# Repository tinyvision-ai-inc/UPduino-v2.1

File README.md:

# UPduino v2.1

## UPDuino v2.1: PCB Design Files, Designs, Documentation

The UPDuino v2.1 is a small, low cost FPGA board, built with license from Lattice Semiconductor. The board features an on-board FPGA programmer, flash and LED with all pins brought out to easy to use 0.1" header pins for fast prototyping.

The tinyVision.ai UPduino v2.1 Board Features:

* Lattice UltraPlus ICE40UP5K FPGA with 5.3K LUTs, 1Mb SPRAM, 120Kb DPRAM, 8 Multipliers
* FTDI FT232H USB to SPI Device
* 30 GPIO on 0.1” headers
* 4MB SPI Flash
* RGB LED
* On board 3.3V and 1.2V Regulators, can supply 3.3V to your project
* Open source schematic and layout using Eagle PCB design tools
* Integrated into the open source [APIO toolchain](https://github.com/FPGAwars/apio)
* Improved USB footprint to minimize connectors ripping off the board

### Please fill out the [next generation survey](https://www.surveymonkey.com/r/HH536D8) to suggest improvements to this board. We really appreciate the feedback and will make improvements as business permits!

You can buy the board here:

## Useful links
* [osresearch](https://github.com/osresearch/up5k): large collection of very useful code and a good overview.
* [UPduino FPGA tutorial using APIO](https://blog.idorobots.org/entries/upduino-fpga-tutorial.html)
* [A very detailed blog on implementing a RISCV in the FPGA](https://pingu98.wordpress.com/2019/04/08/how-to-build-your-own-cpu-from-scratch-inside-an-fpga/)
* [FuPY](https://fupy.github.io/) MicroPython on FPGA's!
* [Migen](https://github.com/m-labs/migen) Python as a High Level tool to generate HW

## Differences between the v2.0 and v2.1 hardware
The original design for the UPduino v2.0 was from [GnarlyGrey](http://gnarlygrey.com/). The design for the UPduino was transferred to tinyVision.ai by Lattice Semiconductor recently. The board is already in use for a variety of projects but some improvements were necessary to make this more production friendly. Note that this exercise was a minimal change only!
* Changed soldermask to black to make it easy to identify the v2.0 from v2.1 and also for branding purposes. Added tinyVision logo to silkscreen.
* Replaced micro USB surface mount connector with through hole parts. This reduces the probability of the USB connector ripping off from the PWB.
* Unified resistor and capacitor sizes to 0603 from a mix of 0603/0805 footprints
* Added fiducials to the board for manufacturability
* LED and resonator went end of life. Replaced the LED with [this](https://www.mouser.com/ProductDetail/Broadcom-Avago/ASMB-MTB0-0A3A2?qs=%2Fha2pyFaduiVySQcEVUF3g99inKvemcQFBZprfU%2FW0p9YdxM%252BOGCOQ%3D%3D) one and the resonator with [this](https://www.mouser.com/ProductDetail/Murata-Electronics/CSTNE12M0G550000R0?qs=sGAEpiMZZMsBj6bBr9Q9aVicrFFkOfIYlp58nnUM76JPeseMdQedBQ%3D%3D) one.
* Flash used is the [Winbond W25Q32JVSNIM](https://www.mouser.com/ProductDetail/Winbond/W25Q32JVSNIM?qs=sGAEpiMZZMtI%252BQ06EiAoG4%252BhDIVn9lGKlH%2FgDg3lStQ%3D)
* Boards are built in Carlsbad, CA from parts sourced from Digikey/Mouser so known good, non-recycled parts are used. We use a cool [vapor phase reflow](https://www.westfloridacomponents.com/blog/vapor-phase-reflow-soldering/)!
* Testing: Each board is inspected using [AOI](https://en.wikipedia.org/wiki/Automated_optical_inspection) to ensure all parts are placed properly. Each board is programmed with a blinking LED to ensure the parts come up and the LED is alive. Also the FTDI EEPROM is programmed with some details.

## Announcing v3.0!
Thank you for the continued feedback which has been incorporated into the [new 3.0 design ](https://github.com/tinyvision-ai-inc/UPduino-v3.0)

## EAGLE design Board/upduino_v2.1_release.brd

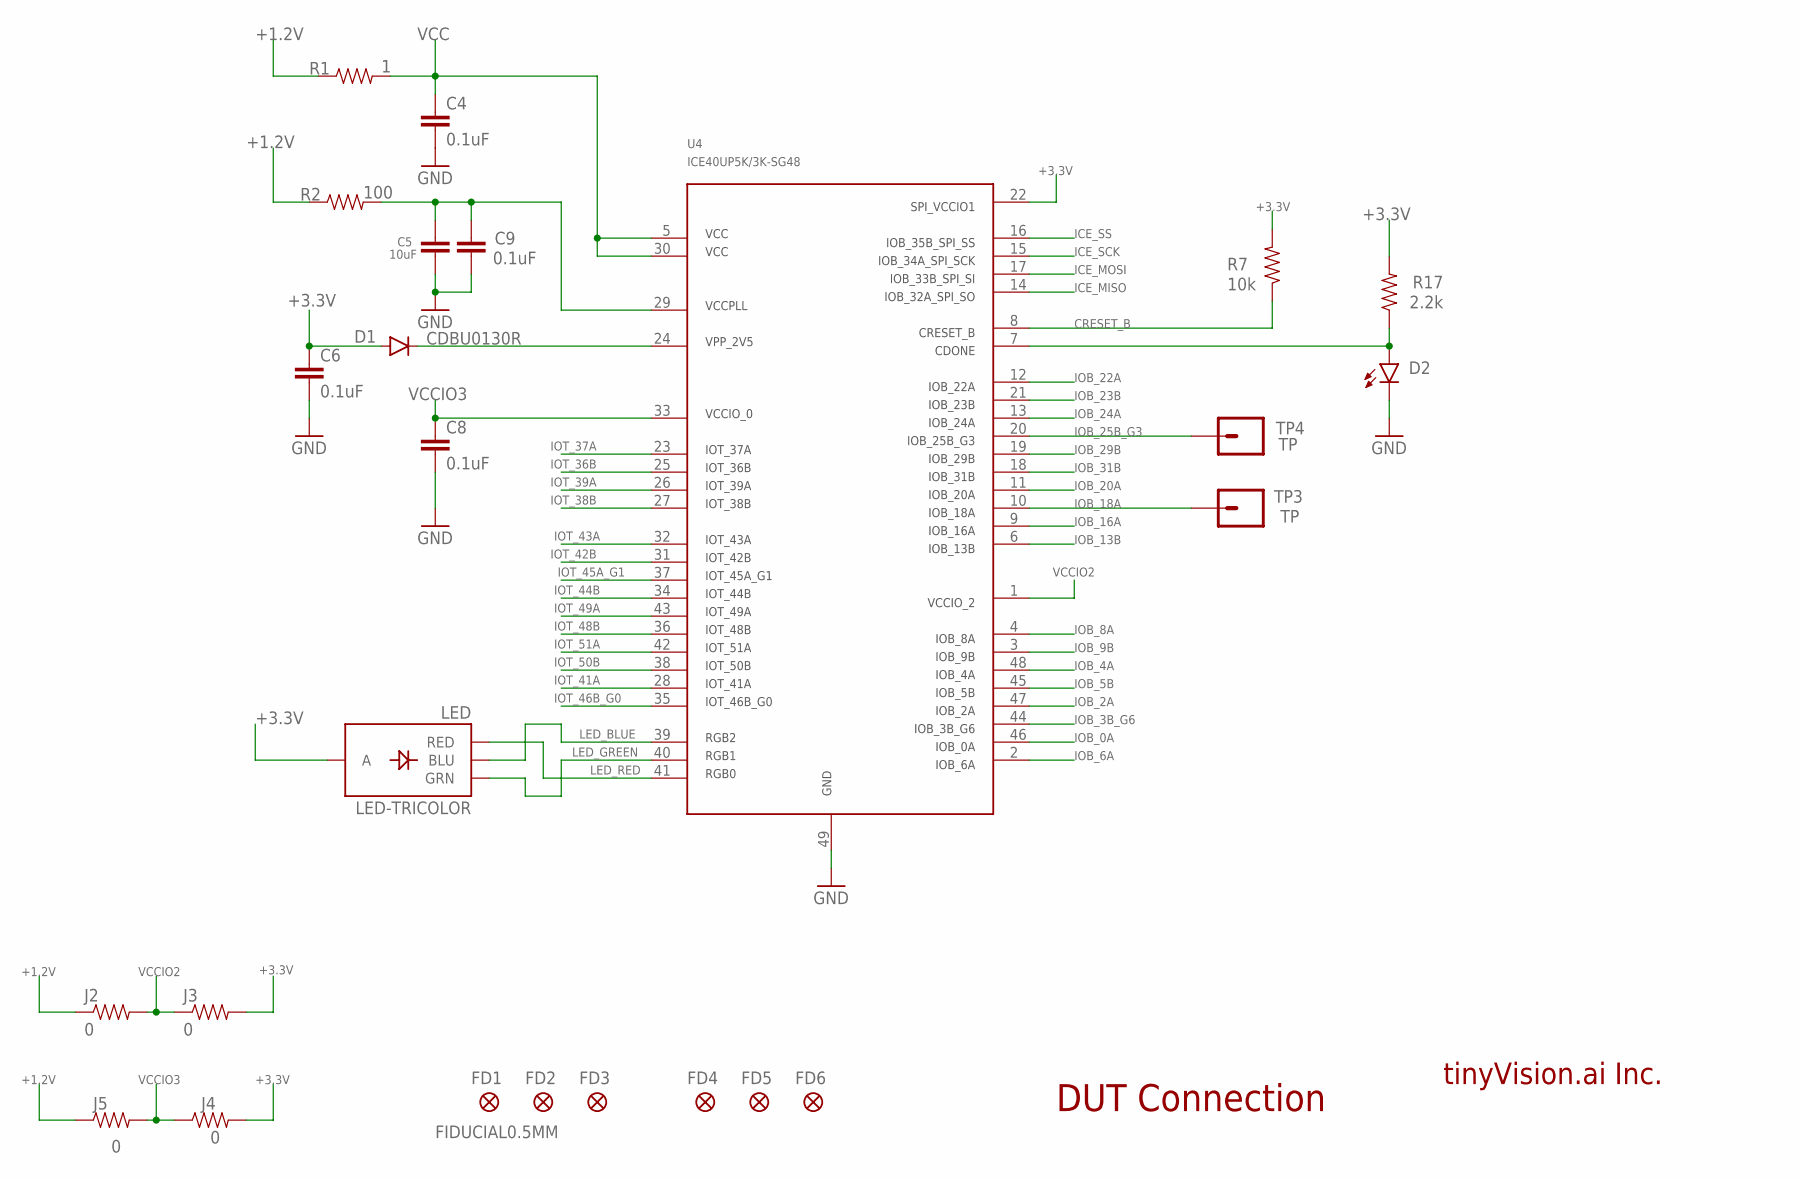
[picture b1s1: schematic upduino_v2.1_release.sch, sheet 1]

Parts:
C4, C6, C8, C9: 0.1uF; 0603-CAP
C5: 10uF; 0603-CAP
D1: CDBU0130R; SOD523
D2: LED0603; LED-0603
FD1, FD2, FD3, FD4, FD5, FD6: FIDUCIAL0.5MM; FIDUCIAL_0.5MM
J2, J3, J4, J5: 0; 0603-RES
LED: LED-TRICOLOR; LED-TRICOLOR-SMD
R1: 1; 0603-RES
R2: 100; 0603-RES
R7: 10k; 0603-RES
R17: 2.2k; 0603-RES
TP3, TP4: TP
U4: ICE40UP5K/3K-SG48

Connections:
+1.2V: J2.1, J5.1, R1.1, R2.1; also elsewhere on the board
+3.3V: C6.1, D1.A, J3.2, J4.2, LED.A, R7.2, R17.2, U4.22; also elsewhere on the board
CRESET_B: R7.1, U4.8; also elsewhere on the board
GND: C4.2, C5.2, C6.2, C8.2, C9.2, D2.C, U4.49; also elsewhere on the board
ICE_MISO: U4.14; also elsewhere on the board
ICE_MOSI: U4.17; also elsewhere on the board
ICE_SCK: U4.15; also elsewhere on the board
ICE_SS: U4.16; also elsewhere on the board
IOB_0A: U4.46; also elsewhere on the board
IOB_2A: U4.47; also elsewhere on the board
IOB_3B_G6: U4.44; also elsewhere on the board
IOB_4A: U4.48; also elsewhere on the board
IOB_5B: U4.45; also elsewhere on the board
IOB_6A: U4.2; also elsewhere on the board
IOB_8A: U4.4; also elsewhere on the board
IOB_9B: U4.3; also elsewhere on the board
IOB_13B: U4.6; also elsewhere on the board
IOB_16A: U4.9; also elsewhere on the board
IOB_18A: TP3.1, U4.10
IOB_20A: U4.11; also elsewhere on the board
IOB_22A: U4.12; also elsewhere on the board
IOB_23B: U4.21; also elsewhere on the board
IOB_24A: U4.13; also elsewhere on the board
IOB_25B_G3: TP4.1, U4.20
IOB_29B: U4.19; also elsewhere on the board
IOB_31B: U4.18; also elsewhere on the board
IOT_36B: U4.25; also elsewhere on the board
IOT_37A: U4.23; also elsewhere on the board
IOT_38B: U4.27; also elsewhere on the board
IOT_39A: U4.26; also elsewhere on the board
IOT_41A: U4.28; also elsewhere on the board
IOT_42B: U4.31; also elsewhere on the board
IOT_43A: U4.32; also elsewhere on the board
IOT_44B: U4.34; also elsewhere on the board
IOT_45A_G1: U4.37; also elsewhere on the board
IOT_46B_G0: U4.35; also elsewhere on the board
IOT_48B: U4.36; also elsewhere on the board
IOT_49A: U4.43; also elsewhere on the board
IOT_50B: U4.38; also elsewhere on the board
IOT_51A: U4.42; also elsewhere on the board
LED_BLUE: LED.B (BLU), U4.39
LED_GREEN: LED.G (GRN), U4.40
LED_RED: LED.R (RED), U4.41
unnamed: C5.1, C9.1, R2.2, U4.29
unnamed: D1.C, U4.24
unnamed: D2.A, R17.1, U4.7
VCC: C4.1, R1.2, U4.5, U4.30
VCCIO2: J2.2, J3.1, U4.1
VCCIO3: C8.1, J4.1, J5.2, U4.33

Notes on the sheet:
DUT Connection
tinyVision.ai Inc.

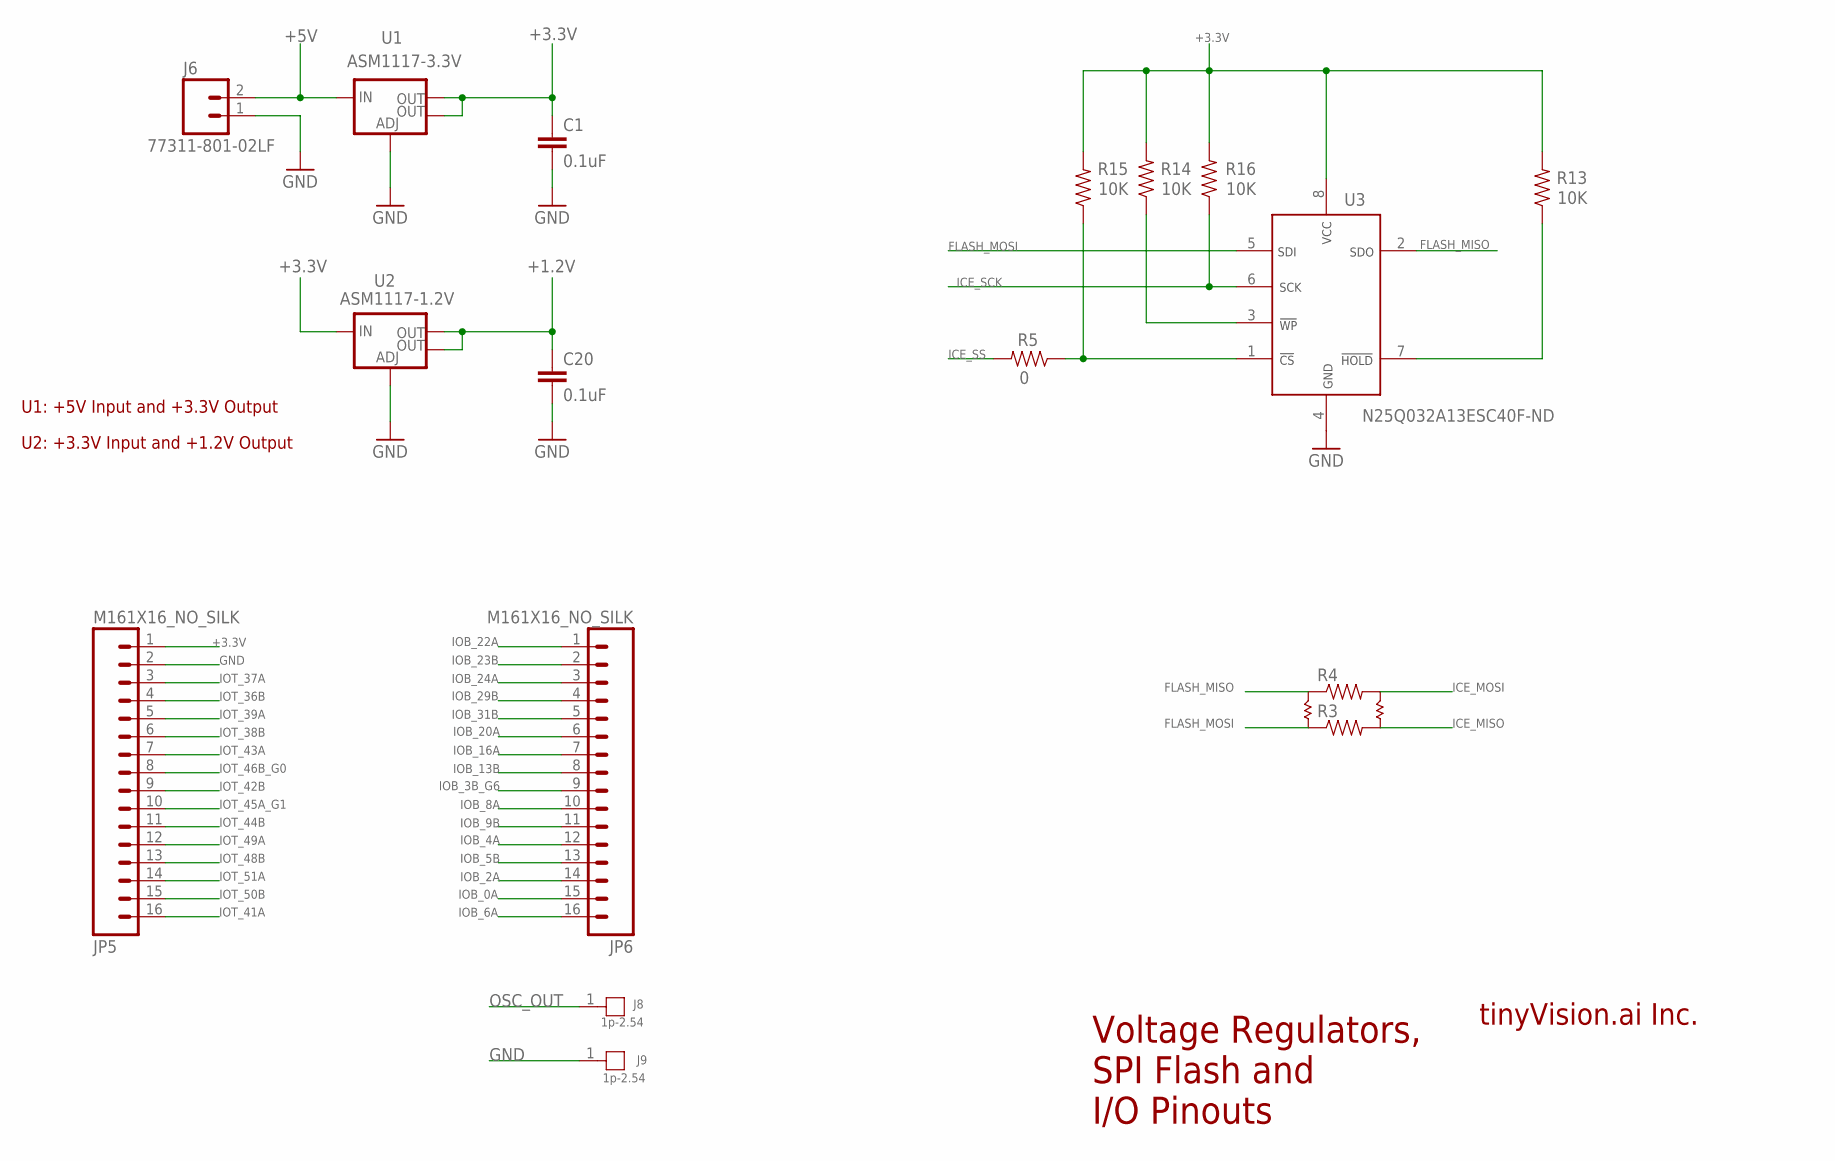
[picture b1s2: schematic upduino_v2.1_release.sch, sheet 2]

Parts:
C1, C20: 0.1uF; 0603-CAP
J6: 77311-801-02LF; 1X02
J8, J9: 1p-2.54; 1P-65/35MIL
JP5, JP6: M161X16_NO_SILK; 1X16_NO_SILK
R3, R4: RESISTOR0603; 0603-RES
R5: 0; 0603-RES
R13, R14, R15, R16: 10K; 0603-RES
U1: ASM1117-3.3V; SOT223
U2: ASM1117-1.2V; SOT223
U3: N25Q032A13ESC40F-ND; SO8; MPN N25Q032A13ESC40F-ND

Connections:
+1.2V: C20.1, U2.2 (OUT), U2.4 (OUT); also elsewhere on the board
+3.3V: C1.1, JP5.1, R13.2, R14.2, R15.2, R16.2, U1.2 (OUT), U1.4 (OUT), U2.3 (IN), U3.8; also elsewhere on the board
+5V: J6.2, U1.3 (IN); also elsewhere on the board
FLASH_MISO: R4.1, U3.2; also elsewhere on the board
FLASH_MOSI: R3.1, U3.5; also elsewhere on the board
GND: C1.2, C20.2, J6.1, J9.1, JP5.2, U1.1 (ADJ), U2.1 (ADJ), U3.4; also elsewhere on the board
ICE_MISO: R3.2; also elsewhere on the board
ICE_MOSI: R4.2; also elsewhere on the board
ICE_SCK: R16.1, U3.6; also elsewhere on the board
ICE_SS: R5.2; also elsewhere on the board
IOB_0A: JP6.15; also elsewhere on the board
IOB_2A: JP6.14; also elsewhere on the board
IOB_3B_G6: JP6.9; also elsewhere on the board
IOB_4A: JP6.12; also elsewhere on the board
IOB_5B: JP6.13; also elsewhere on the board
IOB_6A: JP6.16; also elsewhere on the board
IOB_8A: JP6.10; also elsewhere on the board
IOB_9B: JP6.11; also elsewhere on the board
IOB_13B: JP6.8; also elsewhere on the board
IOB_16A: JP6.7; also elsewhere on the board
IOB_20A: JP6.6; also elsewhere on the board
IOB_22A: JP6.1; also elsewhere on the board
IOB_23B: JP6.2; also elsewhere on the board
IOB_24A: JP6.3; also elsewhere on the board
IOB_29B: JP6.4; also elsewhere on the board
IOB_31B: JP6.5; also elsewhere on the board
IOT_36B: JP5.4; also elsewhere on the board
IOT_37A: JP5.3; also elsewhere on the board
IOT_38B: JP5.6; also elsewhere on the board
IOT_39A: JP5.5; also elsewhere on the board
IOT_41A: JP5.16; also elsewhere on the board
IOT_42B: JP5.9; also elsewhere on the board
IOT_43A: JP5.7; also elsewhere on the board
IOT_44B: JP5.11; also elsewhere on the board
IOT_45A_G1: JP5.10; also elsewhere on the board
IOT_46B_G0: JP5.8; also elsewhere on the board
IOT_48B: JP5.13; also elsewhere on the board
IOT_49A: JP5.12; also elsewhere on the board
IOT_50B: JP5.15; also elsewhere on the board
IOT_51A: JP5.14; also elsewhere on the board
unnamed: R13.1, U3.7
unnamed: R14.1, U3.3
unnamed: R5.1, R15.1, U3.1
OSC_OUT: J8.1; also elsewhere on the board

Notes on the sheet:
tinyVision.ai Inc.
U1: +5V Input and +3.3V Output
U2: +3.3V Input and +1.2V Output
Voltage Regulators, SPI Flash and I/O Pinouts

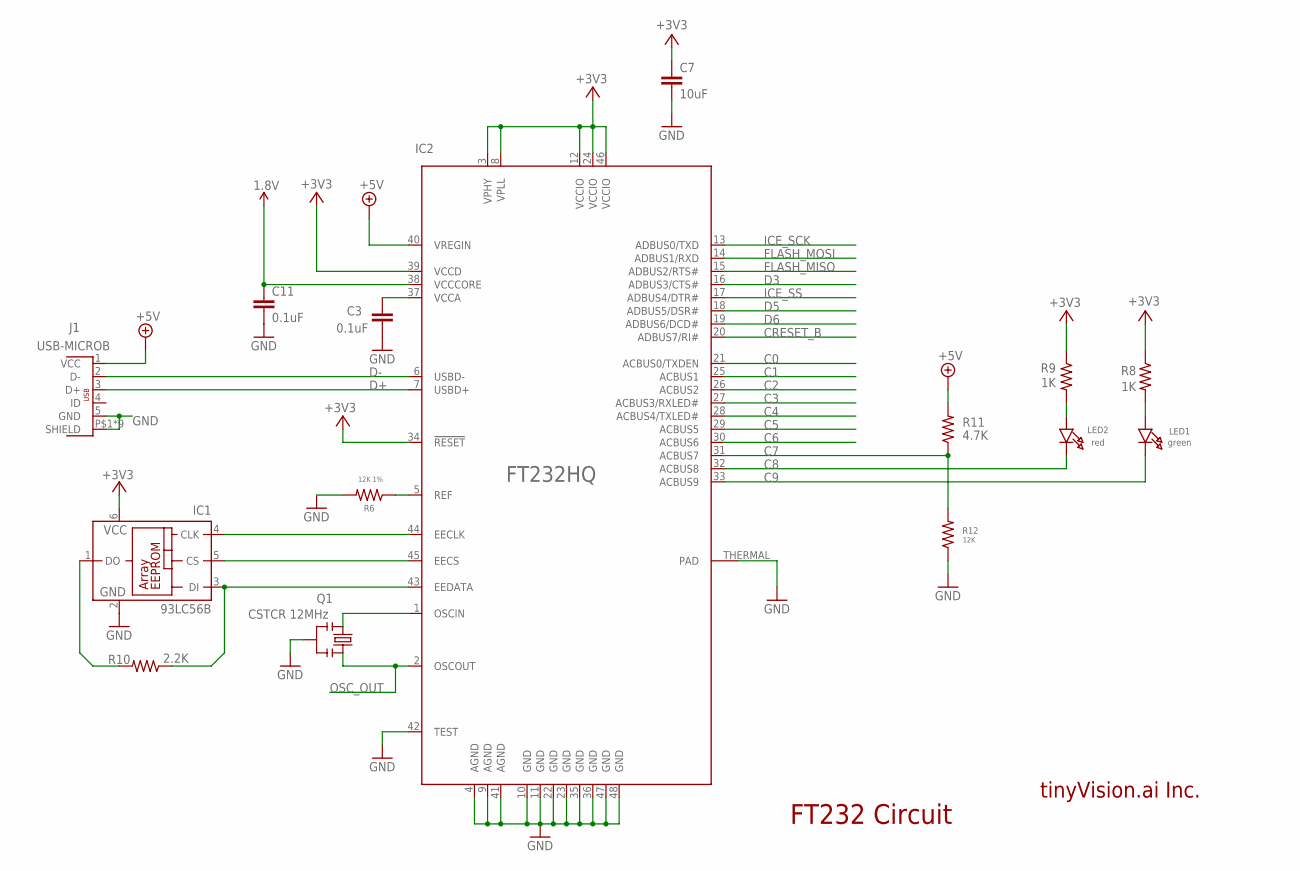
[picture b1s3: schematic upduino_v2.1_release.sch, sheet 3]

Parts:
C3, C11: 0.1uF; 0603-CAP
C7: 10uF; 0603-CAP
IC1: 93LC56B; SOT23-6
IC2: FT232HQ; QFN48_8MM
J1: USB-MICROB; USB_MICROB_10118194-0001LF
LED1: green; CHIPLED_0805_NOOUTLINE
LED2: red; CHIPLED_0805_NOOUTLINE
Q1: CSTCR 12MHz; RESONATOR-SMD
R6: 12K 1%; 0603-RES
R8, R9: 1K; 0603-RES
R10: 2.2K; 0603-RES
R11: 4.7K; 0603-RES
R12: 12K; 0603-RES

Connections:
1.8V: C11.1, IC2.38 (VCCCORE)
+3V3: C7.1, IC1.6 (VCC), IC2.3 (VPHY), IC2.8 (VPLL), IC2.12 (VCCIO), IC2.24 (VCCIO), IC2.34 (!RESET), IC2.39 (VCCD), IC2.46 (VCCIO), R8.1, R9.1
+5V: IC2.40 (VREGIN), J1.1 (VCC), R11.2; also elsewhere on the board
C0: IC2.21 (ACBUS0/TXDEN)
C1: IC2.25 (ACBUS1)
C2: IC2.26 (ACBUS2)
C3: IC2.27 (ACBUS3/RXLED#)
C4: IC2.28 (ACBUS4/TXLED#)
C5: IC2.29 (ACBUS5)
C6: IC2.30 (ACBUS6)
C7: IC2.31 (ACBUS7), R11.1, R12.2
C8: IC2.32 (ACBUS8), LED2.C
C9: IC2.33 (ACBUS9), LED1.C
CRESET_B: IC2.20 (ADBUS7/RI#); also elsewhere on the board
D3: IC2.16 (ADBUS3/CTS#)
D5: IC2.18 (ADBUS5/DSR#)
D6: IC2.19 (ADBUS6/DCD#)
D+: IC2.7 (USBD+), J1.3 (D+)
D-: IC2.6 (USBD-), J1.2 (D-)
FLASH_MISO: IC2.15 (ADBUS2/RTS#); also elsewhere on the board
FLASH_MOSI: IC2.14 (ADBUS1/RXD); also elsewhere on the board
GND: C3.2, C7.2, C11.2, IC1.2 (GND), IC2.4 (AGND), IC2.9 (AGND), IC2.10 (GND), IC2.11 (GND), IC2.22 (GND), IC2.23 (GND), IC2.35 (GND), IC2.36 (GND), IC2.41 (AGND), IC2.42 (TEST), IC2.47 (GND), IC2.48 (GND), IC2.THERMAL (PAD), J1.5 (GND), J1.P$1 (SHIELD), J1.P$2 (SHIELD), J1.P$3 (SHIELD), J1.P$4 (SHIELD), J1.P$5 (SHIELD), J1.P@1 (SHIELD), J1.P@2 (SHIELD), J1.P@3 (SHIELD), J1.P@4 (SHIELD), Q1.2, R6.2, R12.1; also elsewhere on the board
ICE_SCK: IC2.13 (ADBUS0/TXD); also elsewhere on the board
ICE_SS: IC2.17 (ADBUS4/DTR#); also elsewhere on the board
unnamed: IC2.1 (OSCIN), Q1.1
unnamed: IC2.5 (REF), R6.1
unnamed: LED2.A, R9.2
unnamed: LED1.A, R8.2
unnamed: IC1.3 (DI), IC2.43 (EEDATA), R10.1
unnamed: IC1.5 (CS), IC2.45 (EECS)
unnamed: IC1.4 (CLK), IC2.44 (EECLK)
unnamed: IC1.1 (DO), R10.2
OSC_OUT: IC2.2 (OSCOUT), Q1.3; also elsewhere on the board
VCCA: C3.1, IC2.37 (VCCA)

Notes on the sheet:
FT232 Circuit
tinyVision.ai Inc.

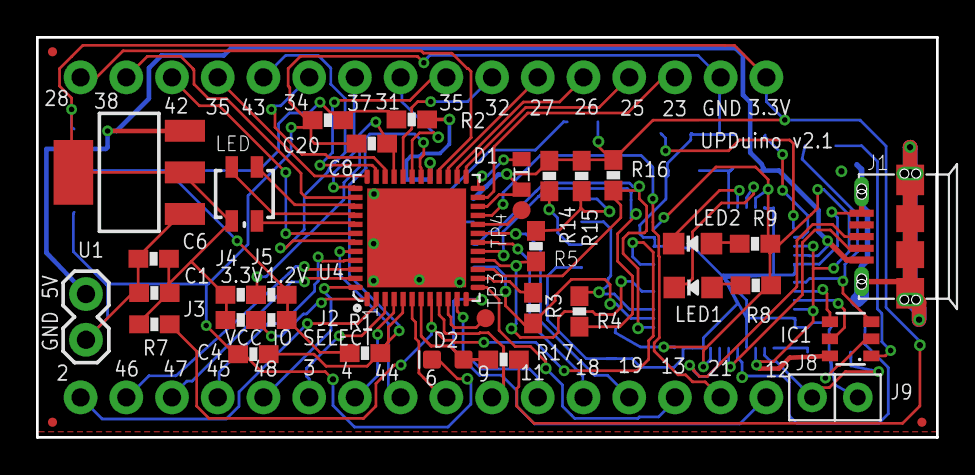
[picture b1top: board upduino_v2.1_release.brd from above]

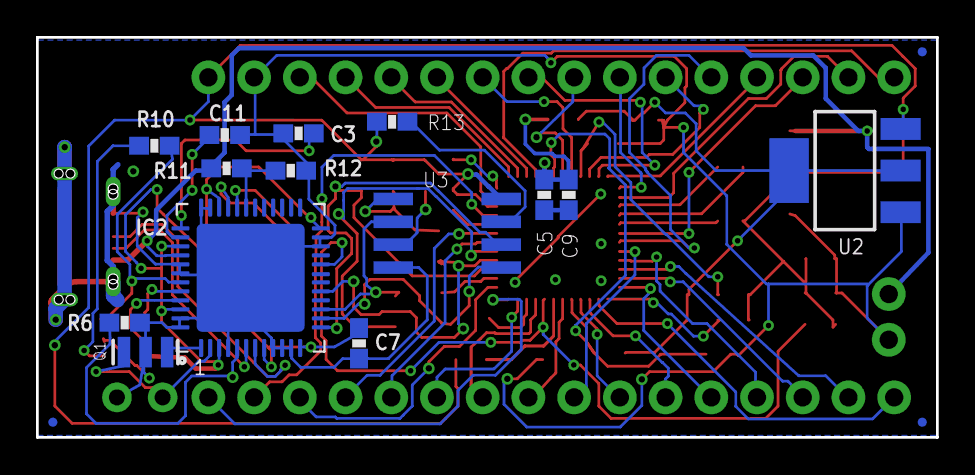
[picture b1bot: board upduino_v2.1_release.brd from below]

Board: 2 copper layers, 50.0 x 22.2 mm, 57 parts (17 on the bottom side), 72 nets.

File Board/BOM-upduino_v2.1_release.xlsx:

Parts | Description | Value | Package | Qty
C1, C3, C4, C6, C8, C9, C11, C20 | Capacitor | 0.1uF | 0603-CAP | 8
C5, C7 | Capacitor | 10uF | 0603-CAP | 2
D1 |  | CDBU0130R | SOD523 | 1
D2 | LED (Generic) |  | LED-0603 | 1
IC1 | 8K Microwire Compatible Serial EEPROM MICRO | 93LC56B | SOT23-6 | 1
IC2 |  | FT232HQ | QFN48_8MM | 1
J1 | CONN RCPT STD MICRO USB TYPE AB | USB-MICROB | USB_MICROB_10118194-0001LF | 1
J2, J3, J4, J5 | Resistor | 0 | 0603-RES | 4
J6 | Standard 2-pin 0.1" header | 77311-801-02LF | 1X02 | 1
J8, J9 | 320030026 | 1p-2.54 | 1P-65/35MIL | 2
JP5, JP6 | 1x16 .1" header | M161X16_NO_SILK | 1X16_NO_SILK | 2
LED | Tri-Color LED SMD | LED-TRICOLOR | LED-TRICOLOR-SMD | 1
LED1 | LED | green | CHIPLED_0805_NOOUTLINE | 1
LED2 | LED | red | CHIPLED_0805_NOOUTLINE | 1
Q1 | Resonator | CSTCR 12MHz | RESONATOR-SMD | 1
R1 | Resistor | 1 | 0603-RES | 1
R10 | Resistor | 2.2K | 0603-RES | 1
R11 | Resistor | 4.7K | 0603-RES | 1
R12 | Resistor | 12K | 0603-RES | 1
R13, R14, R15, R16 | Resistor | 10K | 0603-RES | 4
R17 | Resistor | 2.2k | 0603-RES | 1
R2 | Resistor | 100 | 0603-RES | 1
R3, R4 | Resistor |  | 0603-RES | 2
R5 | Resistor | 0 | 0603-RES | 1
R6 | Resistor | 12K 1% | 0603-RES | 1
R7 | Resistor | 10k | 0603-RES | 1
R8, R9 | Resistor | 1K | 0603-RES | 2
U1 | Voltage Regulator LM1117 | ASM1117-3.3V | SOT223 | 1
U2 | Voltage Regulator LM1117 | ASM1117-1.2V | SOT223 | 1
U3 |  | N25Q032A13ESC40F-ND | SO8 | 1
U4 |  | ICE40UP5K/3K-SG48 | ICE40UP5K/3K-SG48 | 1

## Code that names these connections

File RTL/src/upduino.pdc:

# The LED pins are on dedicated pins and cannot be modified!
# Note that they are negative logic (write a 0 to turn on).
# Also note that if you're using next-pnr and instantiate the SB_RGBA_DRV
# block, it doesnt matter what these pins are set to as long as they're 
# declared (at least as of version 4b54253!).
set_io -nowarn led_green    39
set_io -nowarn led_blue 40
set_io -nowarn led_red	41

# FTDI chip interface
set_io -nowarn serial_txd 14 # FPGA transmit to USB
set_io -nowarn serial_rxd 15 # FPGA receive from USB
set_io -nowarn spi_cs 16 # Connected to SPI flash, drive high unless using SPI flash!

# If using the FTDI MPSSE engine, the following signals apply
set_io -nowarn spi_sck 15
set_io -nowarn spi_ssn 16 # Shared with the flash
set_io -nowarn spi_mosi 17
set_io -nowarn spi_miso 14

# Normal GPIO pins, left side
set_io -nowarn gpio_23 23
set_io -nowarn gpio_25 25
set_io -nowarn gpio_26 26
set_io -nowarn gpio_27 27
set_io -nowarn gpio_32 32
set_io -nowarn gpio_35 35
set_io -nowarn gpio_31 31
set_io -nowarn gpio_37 37
set_io -nowarn gpio_34 34
set_io -nowarn gpio_43 43
set_io -nowarn gpio_36 36
set_io -nowarn gpio_42 42
set_io -nowarn gpio_38 38
set_io -nowarn gpio_28 28

# Normal GPIO pins, right side
set_io -nowarn gpio_12 12
set_io -nowarn gpio_21 21
set_io -nowarn gpio_13 13
set_io -nowarn gpio_19 19
set_io -nowarn gpio_18 18
set_io -nowarn gpio_11 11
set_io -nowarn gpio_9 9
set_io -nowarn gpio_6 6
set_io -nowarn gpio_44 44
set_io -nowarn gpio_4 4
set_io -nowarn gpio_3 3
set_io -nowarn gpio_48 48
set_io -nowarn gpio_45 45
set_io -nowarn gpio_47 47
set_io -nowarn gpio_46 46
set_io -nowarn gpio_2 2

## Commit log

2019-08-27 Initial checkin
    Initial checkin
2019-08-27 Fixed links
2019-08-29 Added updated schematic and minor text changes
2019-08-29 Added gerbers and schematics
2019-09-05 Deleted temp file
2019-09-16 Added UPduino PCF file and a few links
2019-09-16 Added images
    Added images
2019-09-25 Updated with storefront link
2019-09-25 Added link to survey
2019-09-25 Added release notes for v2.1
2019-09-25 Added section on potential changes
2019-09-30 Create LICENSE
2019-10-08 Updated with part numbers
2019-11-18 Exported step file from Eagle
2019-11-18 Added step file
2019-12-10 Added SensAI/Himax design
2019-12-10 Added training files from reference design
2019-12-10 Added keyword detection
2019-12-11 Removed SensAI due to license limitations
2019-12-11 Update LICENSE
2020-03-11 Add Icestorm makefile and udev rule
2020-03-12 Update README for icestorm build and using udev
2020-03-24 Fixed RGB pin assignments courtesy jchidley
2020-03-24 Fixed pinouts for LED's courtesy jchidley
2020-03-24 Added text description

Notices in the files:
parts and their libraries:
SparkFun-Resistors: Licensing: Creative Commons ShareAlike 4.0 International - https://creativecommons.org/licenses/by-sa/4.0
microbuilder: This work is placed in the public domain, and may be freely used for commercial and non-commercial work with the following conditions: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
